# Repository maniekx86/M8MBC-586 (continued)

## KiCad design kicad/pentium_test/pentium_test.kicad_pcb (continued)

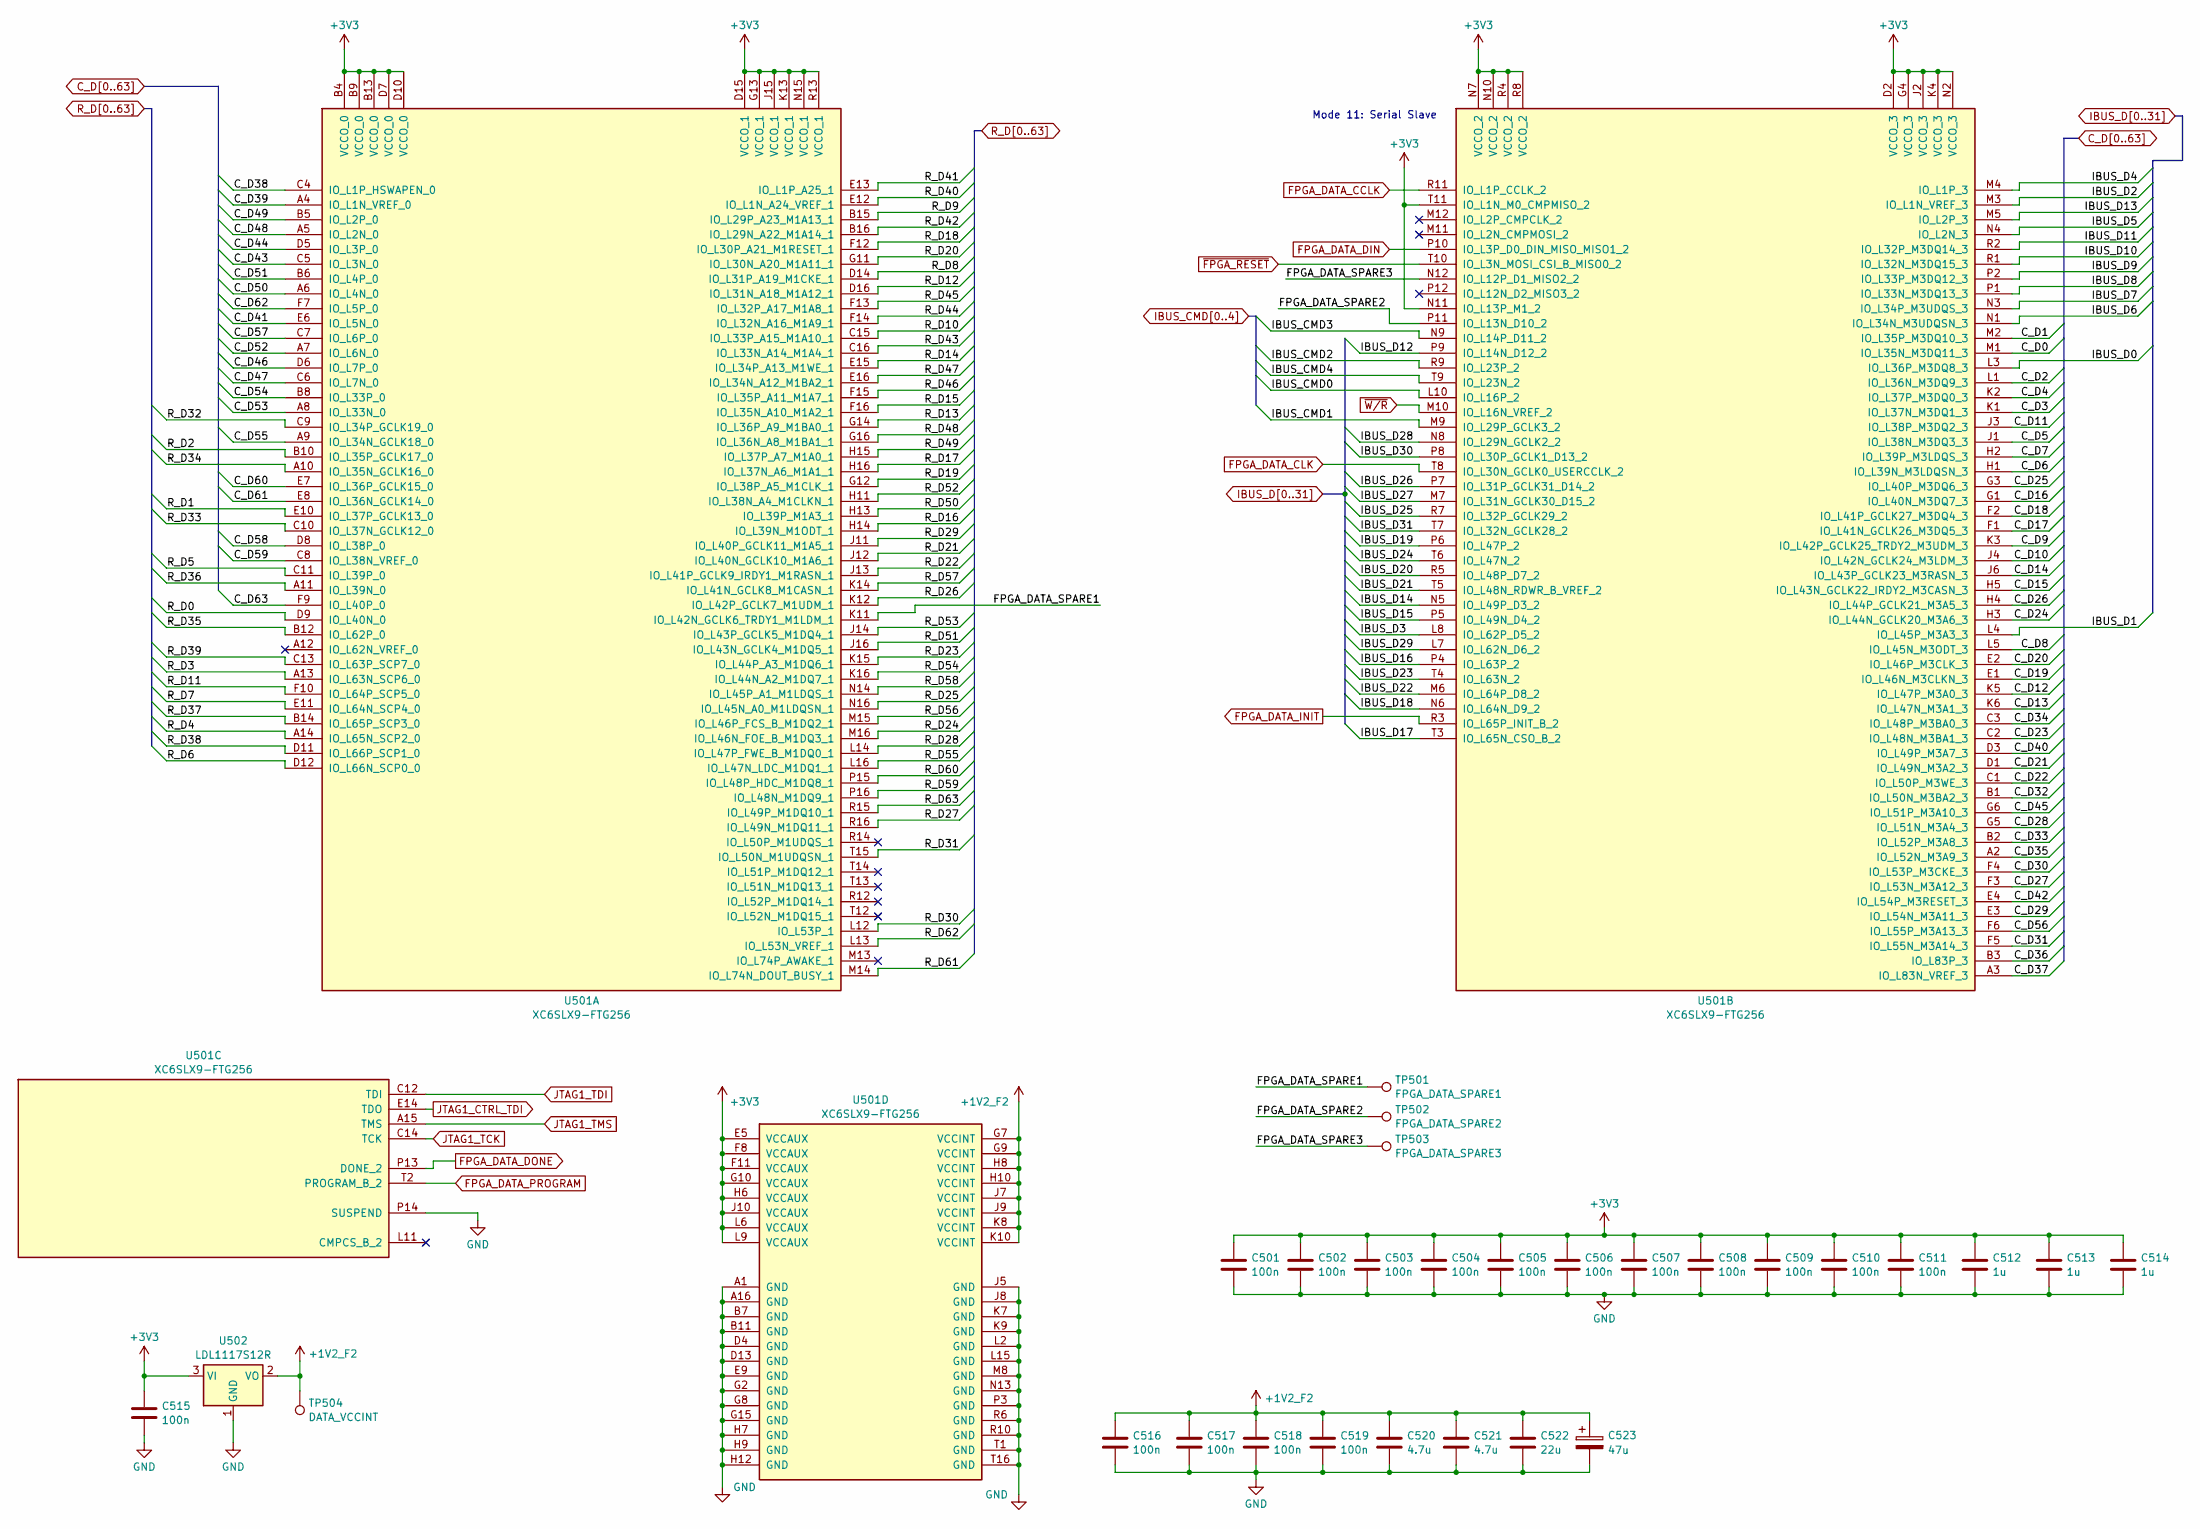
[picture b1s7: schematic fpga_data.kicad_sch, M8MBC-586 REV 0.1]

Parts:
C501, C502, C503, C504, C505, C506, C507, C508, C509, C510, C511, C515, C516, C517, C518, C519: 100n; C_0603_1608Metric
C512, C513, C514: 1u; C_0805_2012Metric
C520, C521: 4.7u; C_0603_1608Metric
C522: 22u; C_1206_3216Metric
C523: 47u; CP_Radial_D5.0mm_P2.50mm
TP501: FPGA_DATA_SPARE1; TestPoint_Pad_D1.0mm
TP502: FPGA_DATA_SPARE2; TestPoint_Pad_D1.0mm
TP503: FPGA_DATA_SPARE3; TestPoint_Pad_D1.0mm
TP504: DATA_VCCINT; TestPoint_Pad_D1.0mm
U501: XC6SLX9-FTG256; Xilinx_FTG256
U502: LDL1117S12R; SOT-223-3_TabPin2

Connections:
+1V2_F2: C516.1, C517.1, C518.1, C519.1, C520.1, C521.1, C522.1, C523.1, TP504.1, U501.G7 (VCCINT), U501.G9 (VCCINT), U501.H8 (VCCINT), U501.H10 (VCCINT), U501.J7 (VCCINT), U501.J9 (VCCINT), U501.K8 (VCCINT), U501.K10 (VCCINT), U502.2 (VO)
+3V3: C501.1, C502.1, C503.1, C504.1, C505.1, C506.1, C507.1, C508.1, C509.1, C510.1, C511.1, C512.1, C513.1, C514.1, C515.1, U501.B4 (VCCO_0), U501.B9 (VCCO_0), U501.B13 (VCCO_0), U501.D2 (VCCO_3), U501.D7 (VCCO_0), U501.D10 (VCCO_0), U501.D15 (VCCO_1), U501.E5 (VCCAUX), U501.F8 (VCCAUX), U501.F11 (VCCAUX), U501.G4 (VCCO_3), U501.G10 (VCCAUX), U501.G13 (VCCO_1), U501.H6 (VCCAUX), U501.J2 (VCCO_3), U501.J10 (VCCAUX), U501.J15 (VCCO_1), U501.K4 (VCCO_3), U501.K13 (VCCO_1), U501.L6 (VCCAUX), U501.L9 (VCCAUX), U501.N2 (VCCO_3), U501.N7 (VCCO_2), U501.N10 (VCCO_2), U501.N11 (IO_L13P_M1_2), U501.N15 (VCCO_1), U501.R4 (VCCO_2), U501.R8 (VCCO_2), U501.R13 (VCCO_1), U501.T11 (IO_L1N_M0_CMPMISO_2), U502.3 (VI); also elsewhere on the board
/fpga_data/FPGA_DATA_SPARE1: TP501.1, U501.K11 (IO_L42N_GCLK6_TRDY1_M1LDM_1)
/fpga_data/FPGA_DATA_SPARE2: TP502.1, U501.P11 (IO_L13N_D10_2)
/fpga_data/FPGA_DATA_SPARE3: TP503.1, U501.N12 (IO_L12P_D1_MISO2_2)
C_D0: U501.M1 (IO_L35N_M3DQ11_3); also elsewhere on the board
C_D1: U501.M2 (IO_L35P_M3DQ10_3); also elsewhere on the board
C_D2: U501.L1 (IO_L36N_M3DQ9_3); also elsewhere on the board
C_D3: U501.K1 (IO_L37N_M3DQ1_3); also elsewhere on the board
C_D4: U501.K2 (IO_L37P_M3DQ0_3); also elsewhere on the board
C_D5: U501.J1 (IO_L38N_M3DQ3_3); also elsewhere on the board
C_D6: U501.H1 (IO_L39N_M3LDQSN_3); also elsewhere on the board
C_D7: U501.H2 (IO_L39P_M3LDQS_3); also elsewhere on the board
C_D8: U501.L5 (IO_L45N_M3ODT_3); also elsewhere on the board
C_D9: U501.K3 (IO_L42P_GCLK25_TRDY2_M3UDM_3); also elsewhere on the board
C_D10: U501.J4 (IO_L42N_GCLK24_M3LDM_3); also elsewhere on the board
C_D11: U501.J3 (IO_L38P_M3DQ2_3); also elsewhere on the board
C_D12: U501.K5 (IO_L47P_M3A0_3); also elsewhere on the board
C_D13: U501.K6 (IO_L47N_M3A1_3); also elsewhere on the board
C_D14: U501.J6 (IO_L43P_GCLK23_M3RASN_3); also elsewhere on the board
C_D15: U501.H5 (IO_L43N_GCLK22_IRDY2_M3CASN_3); also elsewhere on the board
C_D16: U501.G1 (IO_L40N_M3DQ7_3); also elsewhere on the board
C_D17: U501.F1 (IO_L41N_GCLK26_M3DQ5_3); also elsewhere on the board
C_D18: U501.F2 (IO_L41P_GCLK27_M3DQ4_3); also elsewhere on the board
C_D19: U501.E1 (IO_L46N_M3CLKN_3); also elsewhere on the board
C_D20: U501.E2 (IO_L46P_M3CLK_3); also elsewhere on the board
C_D21: U501.D1 (IO_L49N_M3A2_3); also elsewhere on the board
C_D22: U501.C1 (IO_L50P_M3WE_3); also elsewhere on the board
C_D23: U501.C2 (IO_L48N_M3BA1_3); also elsewhere on the board
C_D24: U501.H3 (IO_L44N_GCLK20_M3A6_3); also elsewhere on the board
C_D25: U501.G3 (IO_L40P_M3DQ6_3); also elsewhere on the board
C_D26: U501.H4 (IO_L44P_GCLK21_M3A5_3); also elsewhere on the board
C_D27: U501.F3 (IO_L53N_M3A12_3); also elsewhere on the board
C_D28: U501.G5 (IO_L51N_M3A4_3); also elsewhere on the board
C_D29: U501.E3 (IO_L54N_M3A11_3); also elsewhere on the board
C_D30: U501.F4 (IO_L53P_M3CKE_3); also elsewhere on the board
C_D31: U501.F5 (IO_L55N_M3A14_3); also elsewhere on the board
C_D32: U501.B1 (IO_L50N_M3BA2_3); also elsewhere on the board
C_D33: U501.B2 (IO_L52P_M3A8_3); also elsewhere on the board
C_D34: U501.C3 (IO_L48P_M3BA0_3); also elsewhere on the board
C_D35: U501.A2 (IO_L52N_M3A9_3); also elsewhere on the board
C_D36: U501.B3 (IO_L83P_3); also elsewhere on the board
C_D37: U501.A3 (IO_L83N_VREF_3); also elsewhere on the board
C_D38: U501.C4 (IO_L1P_HSWAPEN_0); also elsewhere on the board
C_D39: U501.A4 (IO_L1N_VREF_0); also elsewhere on the board
C_D40: U501.D3 (IO_L49P_M3A7_3); also elsewhere on the board
C_D41: U501.E6 (IO_L5N_0); also elsewhere on the board
C_D42: U501.E4 (IO_L54P_M3RESET_3); also elsewhere on the board
C_D43: U501.C5 (IO_L3N_0); also elsewhere on the board
C_D44: U501.D5 (IO_L3P_0); also elsewhere on the board
C_D45: U501.G6 (IO_L51P_M3A10_3); also elsewhere on the board
C_D46: U501.D6 (IO_L7P_0); also elsewhere on the board
C_D47: U501.C6 (IO_L7N_0); also elsewhere on the board
C_D48: U501.A5 (IO_L2N_0); also elsewhere on the board
C_D49: U501.B5 (IO_L2P_0); also elsewhere on the board
C_D50: U501.A6 (IO_L4N_0); also elsewhere on the board
C_D51: U501.B6 (IO_L4P_0); also elsewhere on the board
C_D52: U501.A7 (IO_L6N_0); also elsewhere on the board
C_D53: U501.A8 (IO_L33N_0); also elsewhere on the board
C_D54: U501.B8 (IO_L33P_0); also elsewhere on the board
C_D55: U501.A9 (IO_L34N_GCLK18_0); also elsewhere on the board
C_D56: U501.F6 (IO_L55P_M3A13_3); also elsewhere on the board
C_D57: U501.C7 (IO_L6P_0); also elsewhere on the board
C_D58: U501.D8 (IO_L38P_0); also elsewhere on the board
C_D59: U501.C8 (IO_L38N_VREF_0); also elsewhere on the board
C_D60: U501.E7 (IO_L36P_GCLK15_0); also elsewhere on the board
C_D61: U501.E8 (IO_L36N_GCLK14_0); also elsewhere on the board
C_D62: U501.F7 (IO_L5P_0); also elsewhere on the board
C_D63: U501.F9 (IO_L40P_0); also elsewhere on the board
FPGA_DATA_CCLK: U501.R11 (IO_L1P_CCLK_2); also elsewhere on the board
FPGA_DATA_CLK: U501.T8 (IO_L30N_GCLK0_USERCCLK_2); also elsewhere on the board
FPGA_DATA_DIN: U501.P10 (IO_L3P_D0_DIN_MISO_MISO1_2); also elsewhere on the board
FPGA_DATA_DONE: U501.P13 (DONE_2); also elsewhere on the board
FPGA_DATA_INIT: U501.R3 (IO_L65P_INIT_B_2); also elsewhere on the board
FPGA_DATA_PROGRAM: U501.T2 (PROGRAM_B_2); also elsewhere on the board
GND: C501.2, C502.2, C503.2, C504.2, C505.2, C506.2, C507.2, C508.2, C509.2, C510.2, C511.2, C512.2, C513.2, C514.2, C515.2, C516.2, C517.2, C518.2, C519.2, C520.2, C521.2, C522.2, C523.2, U501.A1 (GND), U501.A16 (GND), U501.B7 (GND), U501.B11 (GND), U501.D4 (GND), U501.D13 (GND), U501.E9 (GND), U501.G2 (GND), U501.G8 (GND), U501.G15 (GND), U501.H7 (GND), U501.H9 (GND), U501.H12 (GND), U501.J5 (GND), U501.J8 (GND), U501.K7 (GND), U501.K9 (GND), U501.L2 (GND), U501.L15 (GND), U501.M8 (GND), U501.N13 (GND), U501.P3 (GND), U501.P14 (SUSPEND), U501.R6 (GND), U501.R10 (GND), U501.T1 (GND), U501.T16 (GND), U502.1 (GND); also elsewhere on the board
IBUS_CMD0: U501.L10 (IO_L16P_2); also elsewhere on the board
IBUS_CMD1: U501.M9 (IO_L29P_GCLK3_2); also elsewhere on the board
IBUS_CMD2: U501.R9 (IO_L23P_2); also elsewhere on the board
IBUS_CMD3: U501.N9 (IO_L14P_D11_2); also elsewhere on the board
IBUS_CMD4: U501.T9 (IO_L23N_2); also elsewhere on the board
IBUS_D0: U501.L3 (IO_L36P_M3DQ8_3); also elsewhere on the board
IBUS_D1: U501.L4 (IO_L45P_M3A3_3); also elsewhere on the board
IBUS_D2: U501.M3 (IO_L1N_VREF_3); also elsewhere on the board
IBUS_D3: U501.L8 (IO_L62P_D5_2); also elsewhere on the board
IBUS_D4: U501.M4 (IO_L1P_3); also elsewhere on the board
IBUS_D5: U501.N4 (IO_L2N_3); also elsewhere on the board
IBUS_D6: U501.N1 (IO_L34N_M3UDQSN_3); also elsewhere on the board
IBUS_D7: U501.N3 (IO_L34P_M3UDQS_3); also elsewhere on the board
IBUS_D8: U501.P1 (IO_L33N_M3DQ13_3); also elsewhere on the board
IBUS_D9: U501.P2 (IO_L33P_M3DQ12_3); also elsewhere on the board
IBUS_D10: U501.R1 (IO_L32N_M3DQ15_3); also elsewhere on the board
IBUS_D11: U501.R2 (IO_L32P_M3DQ14_3); also elsewhere on the board
IBUS_D12: U501.P9 (IO_L14N_D12_2); also elsewhere on the board
IBUS_D13: U501.M5 (IO_L2P_3); also elsewhere on the board
IBUS_D14: U501.N5 (IO_L49P_D3_2); also elsewhere on the board
IBUS_D15: U501.P5 (IO_L49N_D4_2); also elsewhere on the board
IBUS_D16: U501.P4 (IO_L63P_2); also elsewhere on the board
IBUS_D17: U501.T3 (IO_L65N_CSO_B_2); also elsewhere on the board
IBUS_D18: U501.N6 (IO_L64N_D9_2); also elsewhere on the board
IBUS_D19: U501.P6 (IO_L47P_2); also elsewhere on the board
IBUS_D20: U501.R5 (IO_L48P_D7_2); also elsewhere on the board
IBUS_D21: U501.T5 (IO_L48N_RDWR_B_VREF_2); also elsewhere on the board
IBUS_D22: U501.M6 (IO_L64P_D8_2); also elsewhere on the board
IBUS_D23: U501.T4 (IO_L63N_2); also elsewhere on the board
IBUS_D24: U501.T6 (IO_L47N_2); also elsewhere on the board
IBUS_D25: U501.R7 (IO_L32P_GCLK29_2); also elsewhere on the board
IBUS_D26: U501.P7 (IO_L31P_GCLK31_D14_2); also elsewhere on the board
IBUS_D27: U501.M7 (IO_L31N_GCLK30_D15_2); also elsewhere on the board
IBUS_D28: U501.N8 (IO_L29N_GCLK2_2); also elsewhere on the board
IBUS_D29: U501.L7 (IO_L62N_D6_2); also elsewhere on the board
IBUS_D30: U501.P8 (IO_L30P_GCLK1_D13_2); also elsewhere on the board
IBUS_D31: U501.T7 (IO_L32N_GCLK28_2); also elsewhere on the board
JTAG1_CTRL_TDI: U501.E14 (TDO); also elsewhere on the board
JTAG1_TCK: U501.C14 (TCK); also elsewhere on the board
JTAG1_TDI: U501.C12 (TDI); also elsewhere on the board
JTAG1_TMS: U501.A15 (TMS); also elsewhere on the board
R_D0: U501.D9 (IO_L40N_0); also elsewhere on the board
R_D1: U501.E10 (IO_L37P_GCLK13_0); also elsewhere on the board
R_D2: U501.B10 (IO_L35P_GCLK17_0); also elsewhere on the board
R_D3: U501.A13 (IO_L63N_SCP6_0); also elsewhere on the board
R_D4: U501.A14 (IO_L65N_SCP2_0); also elsewhere on the board
R_D5: U501.C11 (IO_L39P_0); also elsewhere on the board
R_D6: U501.D12 (IO_L66N_SCP0_0); also elsewhere on the board
R_D7: U501.E11 (IO_L64N_SCP4_0); also elsewhere on the board
R_D8: U501.D14 (IO_L31P_A19_M1CKE_1); also elsewhere on the board
R_D9: U501.B15 (IO_L29P_A23_M1A13_1); also elsewhere on the board
R_D10: U501.C15 (IO_L33P_A15_M1A10_1); also elsewhere on the board
R_D11: U501.F10 (IO_L64P_SCP5_0); also elsewhere on the board
R_D12: U501.D16 (IO_L31N_A18_M1A12_1); also elsewhere on the board
R_D13: U501.G14 (IO_L36P_A9_M1BA0_1); also elsewhere on the board
R_D14: U501.E15 (IO_L34P_A13_M1WE_1); also elsewhere on the board
R_D15: U501.F16 (IO_L35N_A10_M1A2_1); also elsewhere on the board
R_D16: U501.H14 (IO_L39N_M1ODT_1); also elsewhere on the board
R_D17: U501.H16 (IO_L37N_A6_M1A1_1); also elsewhere on the board
R_D18: U501.F12 (IO_L30P_A21_M1RESET_1); also elsewhere on the board
R_D19: U501.G12 (IO_L38P_A5_M1CLK_1); also elsewhere on the board
R_D20: U501.G11 (IO_L30N_A20_M1A11_1); also elsewhere on the board
R_D21: U501.J12 (IO_L40N_GCLK10_M1A6_1); also elsewhere on the board
R_D22: U501.J13 (IO_L41P_GCLK9_IRDY1_M1RASN_1); also elsewhere on the board
R_D23: U501.K15 (IO_L44P_A3_M1DQ6_1); also elsewhere on the board
R_D24: U501.M16 (IO_L46N_FOE_B_M1DQ3_1); also elsewhere on the board
R_D25: U501.N16 (IO_L45N_A0_M1LDQSN_1); also elsewhere on the board
R_D26: U501.K12 (IO_L42P_GCLK7_M1UDM_1); also elsewhere on the board
R_D27: U501.R16 (IO_L49N_M1DQ11_1); also elsewhere on the board
R_D28: U501.L14 (IO_L47P_FWE_B_M1DQ0_1); also elsewhere on the board
R_D29: U501.J11 (IO_L40P_GCLK11_M1A5_1); also elsewhere on the board
R_D30: U501.L12 (IO_L53P_1); also elsewhere on the board
R_D31: U501.T15 (IO_L50N_M1UDQSN_1); also elsewhere on the board
R_D32: U501.C9 (IO_L34P_GCLK19_0); also elsewhere on the board
R_D33: U501.C10 (IO_L37N_GCLK12_0); also elsewhere on the board
R_D34: U501.A10 (IO_L35N_GCLK16_0); also elsewhere on the board
R_D35: U501.B12 (IO_L62P_0); also elsewhere on the board
R_D36: U501.A11 (IO_L39N_0); also elsewhere on the board
R_D37: U501.B14 (IO_L65P_SCP3_0); also elsewhere on the board
R_D38: U501.D11 (IO_L66P_SCP1_0); also elsewhere on the board
R_D39: U501.C13 (IO_L63P_SCP7_0); also elsewhere on the board
R_D40: U501.E12 (IO_L1N_A24_VREF_1); also elsewhere on the board
R_D41: U501.E13 (IO_L1P_A25_1); also elsewhere on the board
R_D42: U501.B16 (IO_L29N_A22_M1A14_1); also elsewhere on the board
R_D43: U501.C16 (IO_L33N_A14_M1A4_1); also elsewhere on the board
R_D44: U501.F14 (IO_L32N_A16_M1A9_1); also elsewhere on the board
R_D45: U501.F13 (IO_L32P_A17_M1A8_1); also elsewhere on the board
R_D46: U501.F15 (IO_L35P_A11_M1A7_1); also elsewhere on the board
R_D47: U501.E16 (IO_L34N_A12_M1BA2_1); also elsewhere on the board
R_D48: U501.G16 (IO_L36N_A8_M1BA1_1); also elsewhere on the board
R_D49: U501.H15 (IO_L37P_A7_M1A0_1); also elsewhere on the board
R_D50: U501.H13 (IO_L39P_M1A3_1); also elsewhere on the board
R_D51: U501.J16 (IO_L43N_GCLK4_M1DQ5_1); also elsewhere on the board
R_D52: U501.H11 (IO_L38N_A4_M1CLKN_1); also elsewhere on the board
R_D53: U501.J14 (IO_L43P_GCLK5_M1DQ4_1); also elsewhere on the board
R_D54: U501.K16 (IO_L44N_A2_M1DQ7_1); also elsewhere on the board
R_D55: U501.L16 (IO_L47N_LDC_M1DQ1_1); also elsewhere on the board
R_D56: U501.M15 (IO_L46P_FCS_B_M1DQ2_1); also elsewhere on the board
R_D57: U501.K14 (IO_L41N_GCLK8_M1CASN_1); also elsewhere on the board
R_D58: U501.N14 (IO_L45P_A1_M1LDQS_1); also elsewhere on the board
R_D59: U501.P16 (IO_L48N_M1DQ9_1); also elsewhere on the board
R_D60: U501.P15 (IO_L48P_HDC_M1DQ8_1); also elsewhere on the board
R_D61: U501.M14 (IO_L74N_DOUT_BUSY_1); also elsewhere on the board
R_D62: U501.L13 (IO_L53N_VREF_1); also elsewhere on the board
R_D63: U501.R15 (IO_L49P_M1DQ10_1); also elsewhere on the board
~FPGA_RESET: U501.T10 (IO_L3N_MOSI_CSI_B_MISO0_2); also elsewhere on the board
~W/R: U501.M10 (IO_L16N_VREF_2); also elsewhere on the board

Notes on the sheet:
Mode 11: Serial Slave

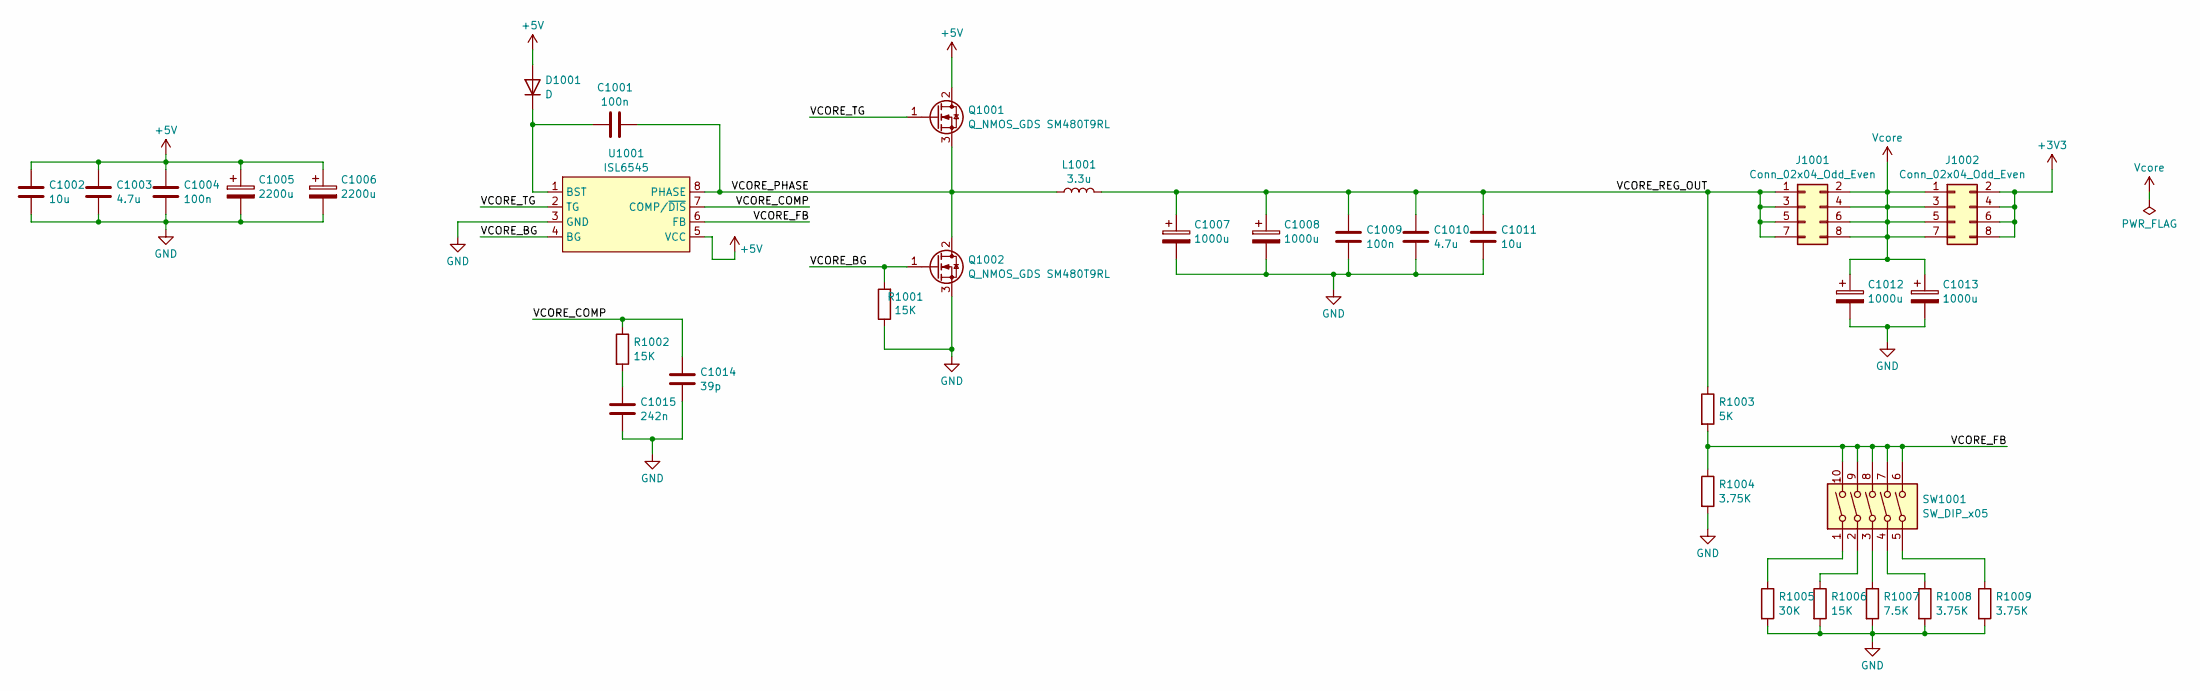
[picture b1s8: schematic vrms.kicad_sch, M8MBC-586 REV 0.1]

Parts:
C1001, C1004, C1009: 100n; C_0603_1608Metric
C1002, C1011: 10u; C_1206_3216Metric
C1003, C1010: 4.7u; C_0805_2012Metric
C1005, C1006: 2200u; CP_Radial_D10.0mm_P5.00mm
C1007, C1008, C1012, C1013: 1000u; CP_Radial_D8.0mm_P3.50mm
C1014: 39p; C_0603_1608Metric
C1015: 242n; C_0603_1608Metric
D1001: D; D_1206_3216Metric
J1001, J1002: Conn_02x04_Odd_Even; PinHeader_2x04_P2.54mm_Vertical
L1001: 3.3u; L_Toroid_Vertical_L16.0mm_W8.0mm_P7.62mm
Q1001, Q1002: Q_NMOS_GDS SM480T9RL; TO-252-2
R1001, R1002, R1006: 15K; R_0603_1608Metric
R1003: 5K; R_0603_1608Metric
R1004, R1008, R1009: 3.75K; R_0603_1608Metric
R1005: 30K; R_0603_1608Metric
R1007: 7.5K; R_0603_1608Metric
SW1001: SW_DIP_x05; SW_DIP_SPSTx05_Slide_9.78x14.88mm_W7.62mm_P2.54mm
U1001: ISL6545; SOIC-8_3.9x4.9mm_P1.27mm

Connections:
+3V3: J1002.2, J1002.4, J1002.6, J1002.8; also elsewhere on the board
+5V: C1002.1, C1003.1, C1004.1, C1005.1, C1006.1, D1001.2 (A), Q1001.2 (D), U1001.5 (VCC); also elsewhere on the board
/vrms/VCORE_BG: Q1002.1 (G), R1001.2, U1001.4 (BG)
/vrms/VCORE_COMP: C1014.1, R1002.1, U1001.7 (COMP/~DIS)
/vrms/VCORE_FB: R1003.2, R1004.1, SW1001.6, SW1001.7, SW1001.8, SW1001.9, SW1001.10, U1001.6 (FB)
/vrms/VCORE_PHASE: C1001.2, L1001.1, Q1001.3 (S), Q1002.2 (D), U1001.8 (PHASE)
/vrms/VCORE_REG_OUT: C1007.1, C1008.1, C1009.1, C1010.1, C1011.1, J1001.1, J1001.3, J1001.5, J1001.7, L1001.2, R1003.1
/vrms/VCORE_TG: Q1001.1 (G), U1001.2 (TG)
GND: C1002.2, C1003.2, C1004.2, C1005.2, C1006.2, C1007.2, C1008.2, C1009.2, C1010.2, C1011.2, C1012.2, C1013.2, C1014.2, C1015.2, Q1002.3 (S), R1001.1, R1004.2, R1005.2, R1006.2, R1007.2, R1008.2, R1009.2, U1001.3 (GND); also elsewhere on the board
unnamed: C1015.1, R1002.2
unnamed: C1001.1, D1001.1 (K), U1001.1 (BST)
unnamed: R1005.1, SW1001.1
unnamed: R1006.1, SW1001.2
unnamed: R1007.1, SW1001.3
unnamed: R1008.1, SW1001.4
unnamed: R1009.1, SW1001.5
Vcore: C1012.1, C1013.1, J1001.2, J1001.4, J1001.6, J1001.8, J1002.1, J1002.3, J1002.5, J1002.7; also elsewhere on the board

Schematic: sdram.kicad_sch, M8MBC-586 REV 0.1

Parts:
C301, C302, C303, C304, C305, C306, C307, C308, C309, C310: 100n; C_0603_1608Metric
C311, C312, C313, C314, C315, C316: 1u; C_0805_2012Metric
C317, C318, C319, C320: 4.7u; C_0805_2012Metric
J301: sdram
R301, R302: 4.7K; R_0603_1608Metric

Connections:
+3V3: C301.1, C302.1, C303.1, C304.1, C305.1, C306.1, C307.1, C308.1, C309.1, C310.1, C311.1, C312.1, C313.1, C314.1, C315.1, C316.1, C317.1, C318.1, C319.1, C320.1, J301.6 (VCC), J301.18 (VCC), J301.26 (VCC), J301.40 (VCC), J301.41 (VCC), J301.49 (VCC), J301.59 (VCC), J301.63 (CKE1), J301.73 (VCC), J301.84 (VCC), J301.90 (VCC), J301.102 (VCC), J301.110 (VCC), J301.124 (VCC), J301.128 (CKE0), J301.133 (VCC), J301.143 (VCC), J301.157 (VCC), J301.168 (VCC), R301.1, R302.1; also elsewhere on the board
GND: C301.2, C302.2, C303.2, C304.2, C305.2, C306.2, C307.2, C308.2, C309.2, C310.2, C311.2, C312.2, C313.2, C314.2, C315.2, C316.2, C317.2, C318.2, C319.2, C320.2, J301.1 (VSS), J301.12 (VSS), J301.23 (VSS), J301.32 (VSS), J301.43 (VSS), J301.54 (VSS), J301.64 (VSS), J301.68 (VSS), J301.78 (VSS), J301.85 (VSS), J301.96 (VSS), J301.107 (VSS), J301.116 (VSS), J301.127 (VSS), J301.138 (VSS), J301.148 (VSS), J301.152 (VSS), J301.162 (VSS), J301.165 (SA0), J301.166 (SA1), J301.167 (SA2); also elsewhere on the board
R_A0: J301.33 (A0); also elsewhere on the board
R_A1: J301.117 (A1); also elsewhere on the board
R_A2: J301.34 (A2); also elsewhere on the board
R_A3: J301.118 (A3); also elsewhere on the board
R_A4: J301.35 (A4); also elsewhere on the board
R_A5: J301.119 (A5); also elsewhere on the board
R_A6: J301.36 (A6); also elsewhere on the board
R_A7: J301.120 (A7); also elsewhere on the board
R_A8: J301.37 (A8); also elsewhere on the board
R_A9: J301.121 (A9); also elsewhere on the board
R_A10: J301.38 (A10(AP)); also elsewhere on the board
R_A11: J301.123 (A11); also elsewhere on the board
R_A12: J301.126 (A12); also elsewhere on the board
R_A13: J301.132 (A13); also elsewhere on the board
R_BA0: J301.122 (BA0); also elsewhere on the board
R_BA1: J301.39 (BA1); also elsewhere on the board
R_CK0: J301.42 (CK0); also elsewhere on the board
R_CK1: J301.125 (CK1); also elsewhere on the board
R_CK2: J301.79 (CK2); also elsewhere on the board
R_CK3: J301.163 (CK3); also elsewhere on the board
R_D0: J301.2 (DQ0); also elsewhere on the board
R_D1: J301.3 (DQ1); also elsewhere on the board
R_D2: J301.4 (DQ2); also elsewhere on the board
R_D3: J301.5 (DQ3); also elsewhere on the board
R_D4: J301.7 (DQ4); also elsewhere on the board
R_D5: J301.8 (DQ5); also elsewhere on the board
R_D6: J301.9 (DQ6); also elsewhere on the board
R_D7: J301.10 (DQ7); also elsewhere on the board
R_D8: J301.11 (DQ8); also elsewhere on the board
R_D9: J301.13 (DQ9); also elsewhere on the board
R_D10: J301.14 (DQ10); also elsewhere on the board
R_D11: J301.15 (DQ11); also elsewhere on the board
R_D12: J301.16 (DQ12); also elsewhere on the board
R_D13: J301.17 (DQ13); also elsewhere on the board
R_D14: J301.19 (DQ14); also elsewhere on the board
R_D15: J301.20 (DQ15); also elsewhere on the board
R_D16: J301.55 (DQ16); also elsewhere on the board
R_D17: J301.56 (DQ17); also elsewhere on the board
R_D18: J301.57 (DQ18); also elsewhere on the board
R_D19: J301.58 (DQ19); also elsewhere on the board
R_D20: J301.60 (DQ20); also elsewhere on the board
R_D21: J301.65 (DQ21); also elsewhere on the board
R_D22: J301.66 (DQ22); also elsewhere on the board
R_D23: J301.67 (DQ23); also elsewhere on the board
R_D24: J301.69 (DQ24); also elsewhere on the board
R_D25: J301.70 (DQ25); also elsewhere on the board
R_D26: J301.71 (DQ26); also elsewhere on the board
R_D27: J301.72 (DQ27); also elsewhere on the board
R_D28: J301.74 (DQ28); also elsewhere on the board
R_D29: J301.75 (DQ29); also elsewhere on the board
R_D30: J301.76 (DQ30); also elsewhere on the board
R_D31: J301.77 (DQ31); also elsewhere on the board
R_D32: J301.86 (DQ32); also elsewhere on the board
R_D33: J301.87 (DQ33); also elsewhere on the board
R_D34: J301.88 (DQ34); also elsewhere on the board
R_D35: J301.89 (DQ35); also elsewhere on the board
R_D36: J301.91 (DQ36); also elsewhere on the board
R_D37: J301.92 (DQ37); also elsewhere on the board
R_D38: J301.93 (DQ38); also elsewhere on the board
R_D39: J301.94 (DQ39); also elsewhere on the board
R_D40: J301.95 (DQ40); also elsewhere on the board
R_D41: J301.97 (DQ41); also elsewhere on the board
R_D42: J301.98 (DQ42); also elsewhere on the board
R_D43: J301.99 (DQ43); also elsewhere on the board
R_D44: J301.100 (DQ44); also elsewhere on the board
R_D45: J301.101 (DQ45); also elsewhere on the board
R_D46: J301.103 (DQ46); also elsewhere on the board
R_D47: J301.104 (DQ47); also elsewhere on the board
R_D48: J301.139 (DQ48); also elsewhere on the board
R_D49: J301.140 (DQ49); also elsewhere on the board
R_D50: J301.141 (DQ50); also elsewhere on the board
R_D51: J301.142 (DQ51); also elsewhere on the board
R_D52: J301.144 (DQ52); also elsewhere on the board
R_D53: J301.149 (DQ53); also elsewhere on the board
R_D54: J301.150 (DQ54); also elsewhere on the board
R_D55: J301.151 (DQ55); also elsewhere on the board
R_D56: J301.153 (DQ56); also elsewhere on the board
R_D57: J301.154 (DQ57); also elsewhere on the board
R_D58: J301.155 (DQ58); also elsewhere on the board
R_D59: J301.156 (DQ59); also elsewhere on the board
R_D60: J301.158 (DQ60); also elsewhere on the board
R_D61: J301.159 (DQ61); also elsewhere on the board
R_D62: J301.160 (DQ62); also elsewhere on the board
R_D63: J301.161 (DQ63); also elsewhere on the board
R_DQMB0: J301.28 (DQMB0); also elsewhere on the board
R_DQMB1: J301.29 (DQMB1); also elsewhere on the board
R_DQMB2: J301.46 (DQMB2); also elsewhere on the board
R_DQMB3: J301.47 (DQMB3); also elsewhere on the board
R_DQMB4: J301.112 (DQMB4); also elsewhere on the board
R_DQMB5: J301.113 (DQMB5); also elsewhere on the board
R_DQMB6: J301.130 (DQMB6); also elsewhere on the board
R_DQMB7: J301.131 (DQMB7); also elsewhere on the board
R_SCL: J301.83 (SCL), R301.2; also elsewhere on the board
R_SDA: J301.82 (SDA), R302.2; also elsewhere on the board
~R_CAS: J301.111 (/CAS); also elsewhere on the board
~R_RAS: J301.115 (/RAS); also elsewhere on the board
~R_S0/1: J301.30 (/S0), J301.114 (/S1); also elsewhere on the board
~R_S2/3: J301.45 (/S2), J301.129 (/S3); also elsewhere on the board
~R_WE: J301.27 (/WE0); also elsewhere on the board

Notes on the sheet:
10x 100nF 0603 +3V3
ECC only
I2C 0x50
4x 4.7uF 0805 +3V3
6x 1uF 0805 +3V3
